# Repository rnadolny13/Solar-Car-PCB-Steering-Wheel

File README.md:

This project is a PCB design for the UWSVT steering wheel. Car operates on CAN BUS, included are buttons such as turn singals, cruise crontrol, push-to-talk, and more. VUSB as well for quick debugging. Designed in KiCad

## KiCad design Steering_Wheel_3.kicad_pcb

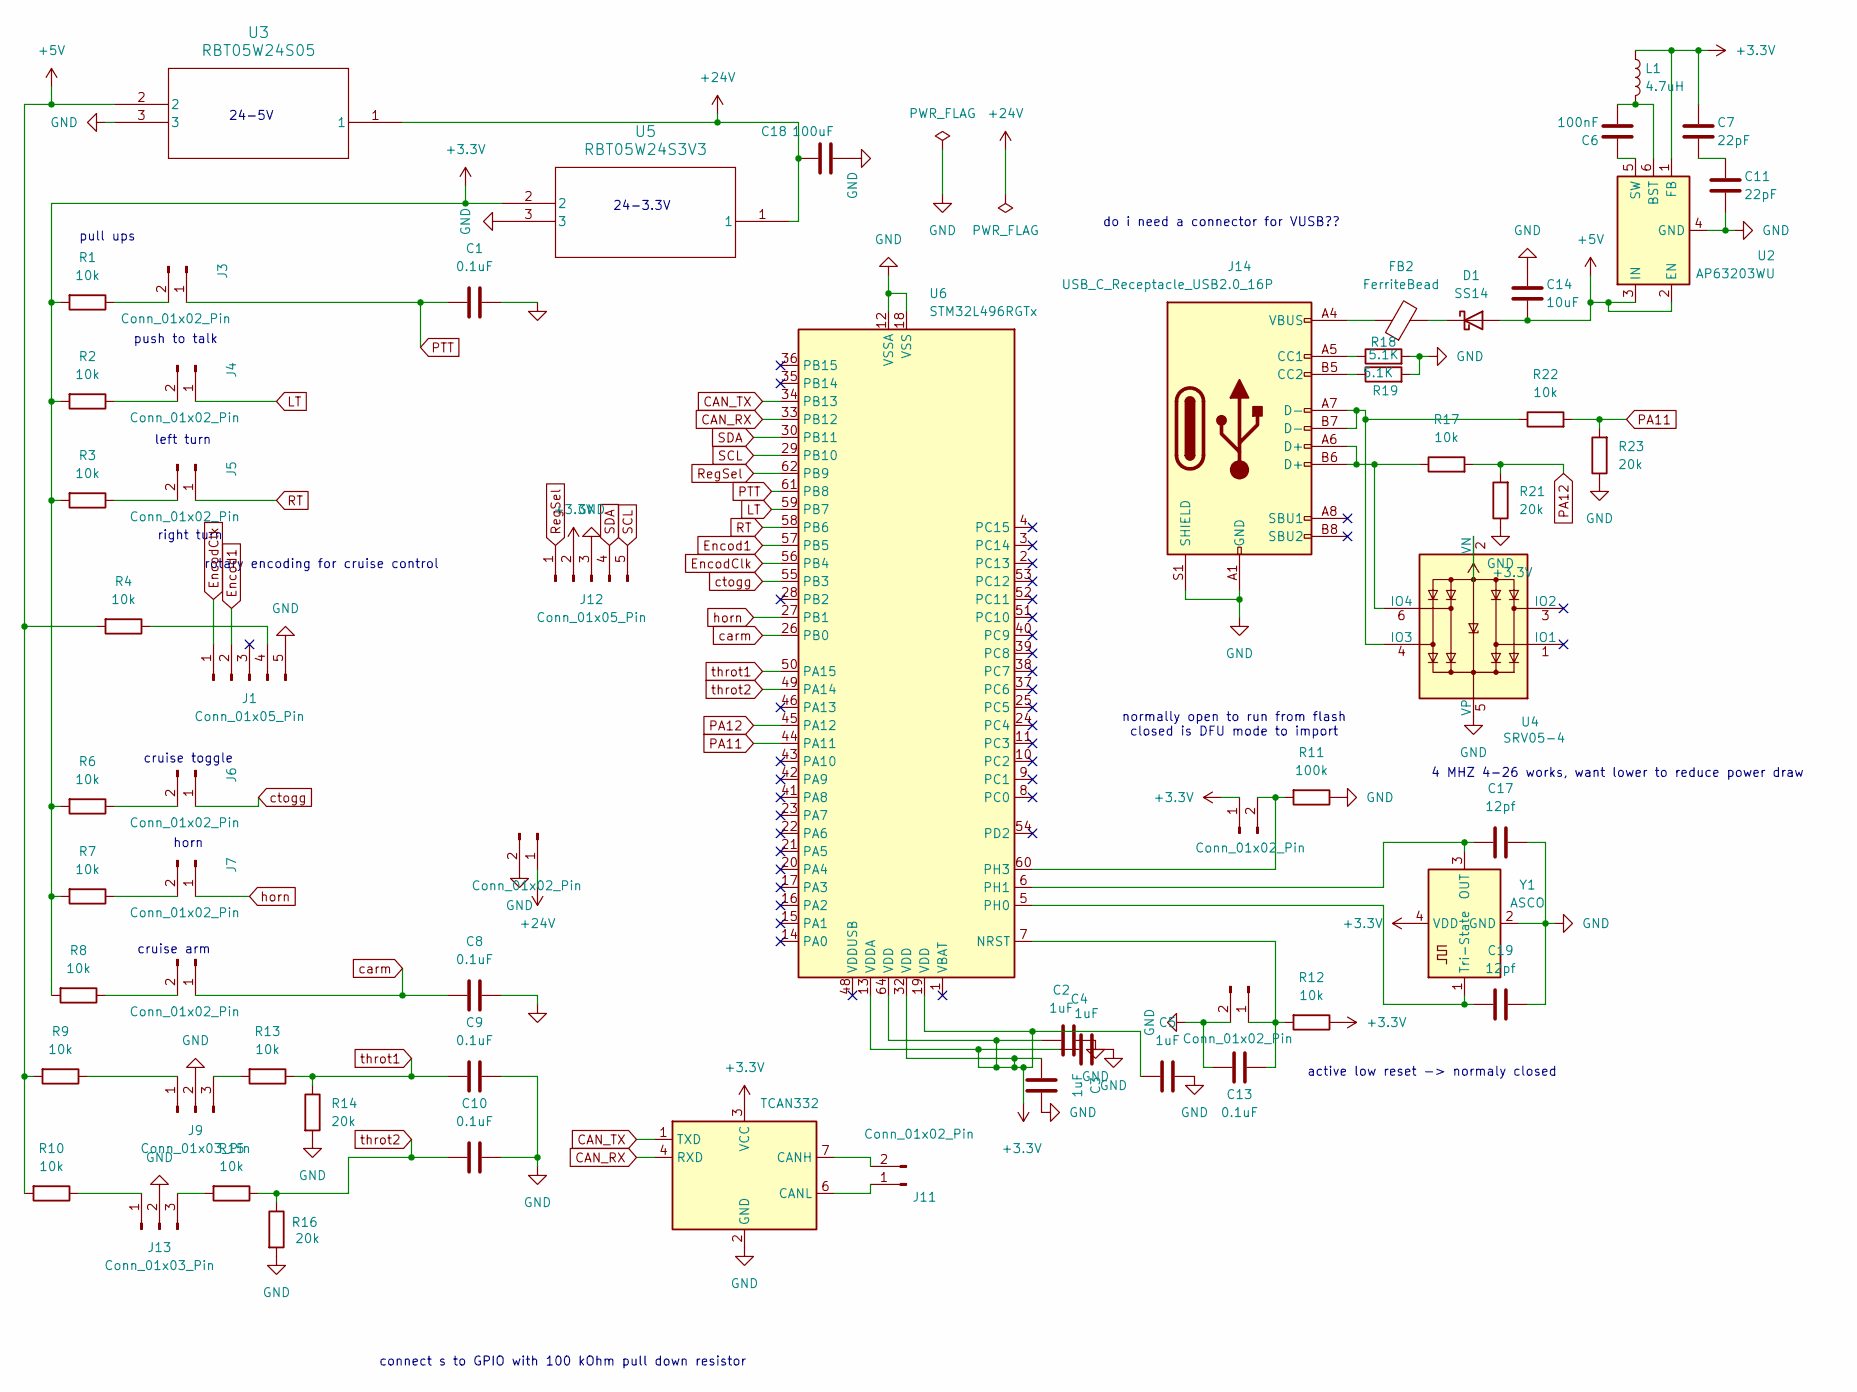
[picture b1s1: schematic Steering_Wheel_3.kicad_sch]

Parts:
C1, C8, C9, C10, C13: 0.1uF; C_0603_1608Metric_Pad1.08x0.95mm_HandSolder
C2, C3, C4, C5: 1uF; C_0805_2012Metric_Pad1.18x1.45mm_HandSolder
C6: 100nF; C_0805_2012Metric_Pad1.18x1.45mm_HandSolder
C7, C11: 22pF; C_0805_2012Metric_Pad1.18x1.45mm_HandSolder
C14: 10uF; C_0805_2012Metric_Pad1.18x1.45mm_HandSolder
C17, C19: 12pf; C_0603_1608Metric_Pad1.08x0.95mm_HandSolder
C18: 100uF; C_1206_3216Metric_Pad1.33x1.80mm_HandSolder
D1: SS14; D_SMA
FB2: FerriteBead; R_1206_3216Metric
J1, J12: Conn_01x05_Pin; PinHeader_1x05_P2.54mm_Vertical
J2, J3, J4, J5, J6, J7, J8, J10, J11, J15: Conn_01x02_Pin; PinHeader_1x02_P2.54mm_Vertical
J9, J13: Conn_01x03_Pin; PinHeader_1x03_P2.54mm_Vertical
J14: USB_C_Receptacle_USB2.0_16P; USB_C_Receptacle_HRO_TYPE-C-31-M-12
L1: 4.7uH; INDC2016X100N - inductor
R1, R2, R3, R4, R6, R7, R8, R9, R10, R12, R13, R15, R17, R22: 10k; R_0402_1005Metric
R11: 100k; R_0402_1005Metric
R14, R16, R21, R23: 20k; R_0402_1005Metric
R18, R19: 5.1K; R_0402_1005Metric
U1: TCAN332; SOIC127P599X175-8N
U2: AP63203WU; TSOT-23-6
U3: RBT05W24S05; DCDC
U4: SRV05-4; SOT-23-6_Handsoldering
U5: RBT05W24S3V3; DCDC
U6: STM32L496RGTx; LQFP-64_10x10mm_P0.5mm
Y1: ASCO; Oscillator_SMD_Abracon_ASCO-4Pin_1.6x1.2mm

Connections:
+3.3V: C2.1, C3.1, C4.1, C5.1, C7.1, J10.1, J12.2, L1.1, R1.2, R2.2, R3.2, R6.2, R7.2, R8.2, R12.1, U1.3 (VCC), U2.1 (FB), U4.2 (VN), U5.2, U6.13 (VDDA), U6.19 (VDD), U6.32 (VDD), U6.64 (VDD), Y1.4 (VDD)
+5V: C14.2, D1.2 (A), R4.2, R9.2, R10.2, U2.2 (EN), U2.3 (IN), U3.2
+24V: C18.1, J15.1, U3.1, U5.1
CAN_RX: U1.4 (RXD), U6.33 (PB12)
CAN_TX: U1.1 (TXD), U6.34 (PB13)
Encod1: J1.2, U6.57 (PB5)
EncodClk: J1.1, U6.56 (PB4)
GND: C1.1, C2.2, C3.2, C4.2, C5.2, C8.1, C9.1, C10.1, C11.2, C13.2, C14.1, C17.1, C18.2, C19.1, J1.5, J2.2, J9.2, J12.3, J13.2, J14.A1 (GND), J14.A12 (GND), J14.B1 (GND), J14.B12 (GND), J14.S1 (SHIELD), J15.2, R11.1, R14.2, R16.2, R18.2, R19.2, R21.1, R23.1, U1.2 (GND), U2.4 (GND), U3.3, U4.5 (VP), U5.3, U6.12 (VSSA), U6.18 (VSS), U6.31 (VSS), U6.47 (VSS), U6.63 (VSS), Y1.2 (GND)
LT: J4.1, U6.59 (PB7)
unnamed: C7.2, C11.1
unnamed: D1.1 (K), FB2.2
unnamed: FB2.1, J14.A4 (VBUS), J14.A9 (VBUS), J14.B4 (VBUS), J14.B9 (VBUS)
unnamed: J1.4, R4.1
unnamed: C13.1, J2.1, R12.2, U6.7 (NRST)
unnamed: J3.2, R1.1
unnamed: J4.2, R2.1
unnamed: J5.2, R3.1
unnamed: J6.2, R6.1
unnamed: J7.2, R7.1
unnamed: J8.2, R8.1
unnamed: J9.1, R9.1
unnamed: J9.3, R13.2
unnamed: J10.2, R11.2, U6.60 (PH3)
unnamed: J11.1, U1.6 (CANL)
unnamed: J11.2, U1.7 (CANH)
unnamed: J13.1, R10.1
unnamed: J13.3, R15.2
unnamed: J14.A5 (CC1), R18.1
unnamed: J14.B5 (CC2), R19.1
unnamed: C6.2, L1.2, U2.6 (BST)
unnamed: C6.1, U2.5 (SW)
unnamed: J14.A7 (D-), J14.B7 (D-), R22.1, U4.4 (IO3)
unnamed: J14.A6 (D+), J14.B6 (D+), R17.1, U4.6 (IO4)
unnamed: C19.2, U6.5 (PH0), Y1.1 (Tri-State)
unnamed: C17.2, U6.6 (PH1), Y1.3 (OUT)
PA11: R22.2, R23.2, U6.44 (PA11)
PA12: R17.2, R21.2, U6.45 (PA12)
PTT: C1.2, J3.1, U6.61 (PB8)
RT: J5.1, U6.58 (PB6)
RegSel: J12.1, U6.62 (PB9)
SCL: J12.5, U6.29 (PB10)
SDA: J12.4, U6.30 (PB11)
carm: C8.2, J8.1, U6.26 (PB0)
ctogg: J6.1, U6.55 (PB3)
horn: J7.1, U6.27 (PB1)
throt1: C9.2, R13.1, R14.1, U6.50 (PA15)
throt2: C10.2, R15.1, R16.1, U6.49 (PA14)

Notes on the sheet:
normally open to run from flash closed is DFU mode to import
push to talk
4 MHZ 4-26 works, want lower to reduce power draw
do i need a connector for VUSB??
pull ups
connect s to GPIO with 100 kOhm pull down resistor
left turn
cruise toggle
active low reset -> normaly closed
24-5V
rotary encoding for cruise control
horn
24-3.3V
cruise arm
right turn

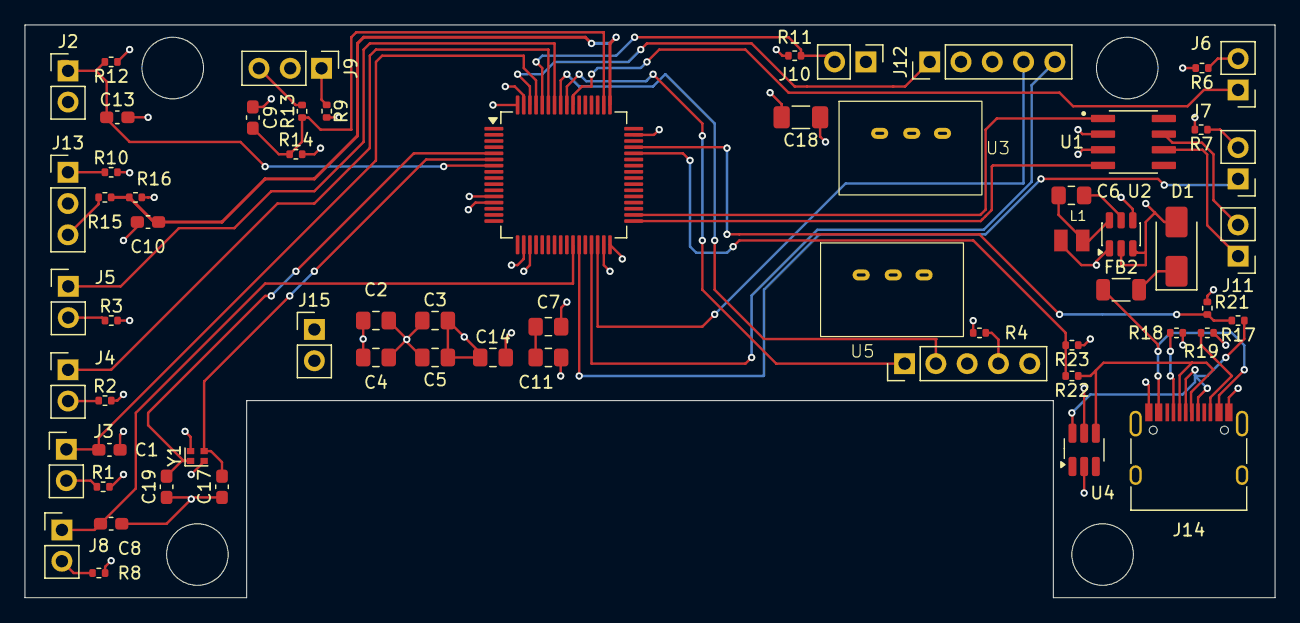
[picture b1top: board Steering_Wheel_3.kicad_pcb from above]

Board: 6 copper layers, 101.5 x 46.5 mm, 62 parts (0 on the bottom side), 47 nets.

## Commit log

2025-12-30 Update README.md
    Added design software information to project description.
